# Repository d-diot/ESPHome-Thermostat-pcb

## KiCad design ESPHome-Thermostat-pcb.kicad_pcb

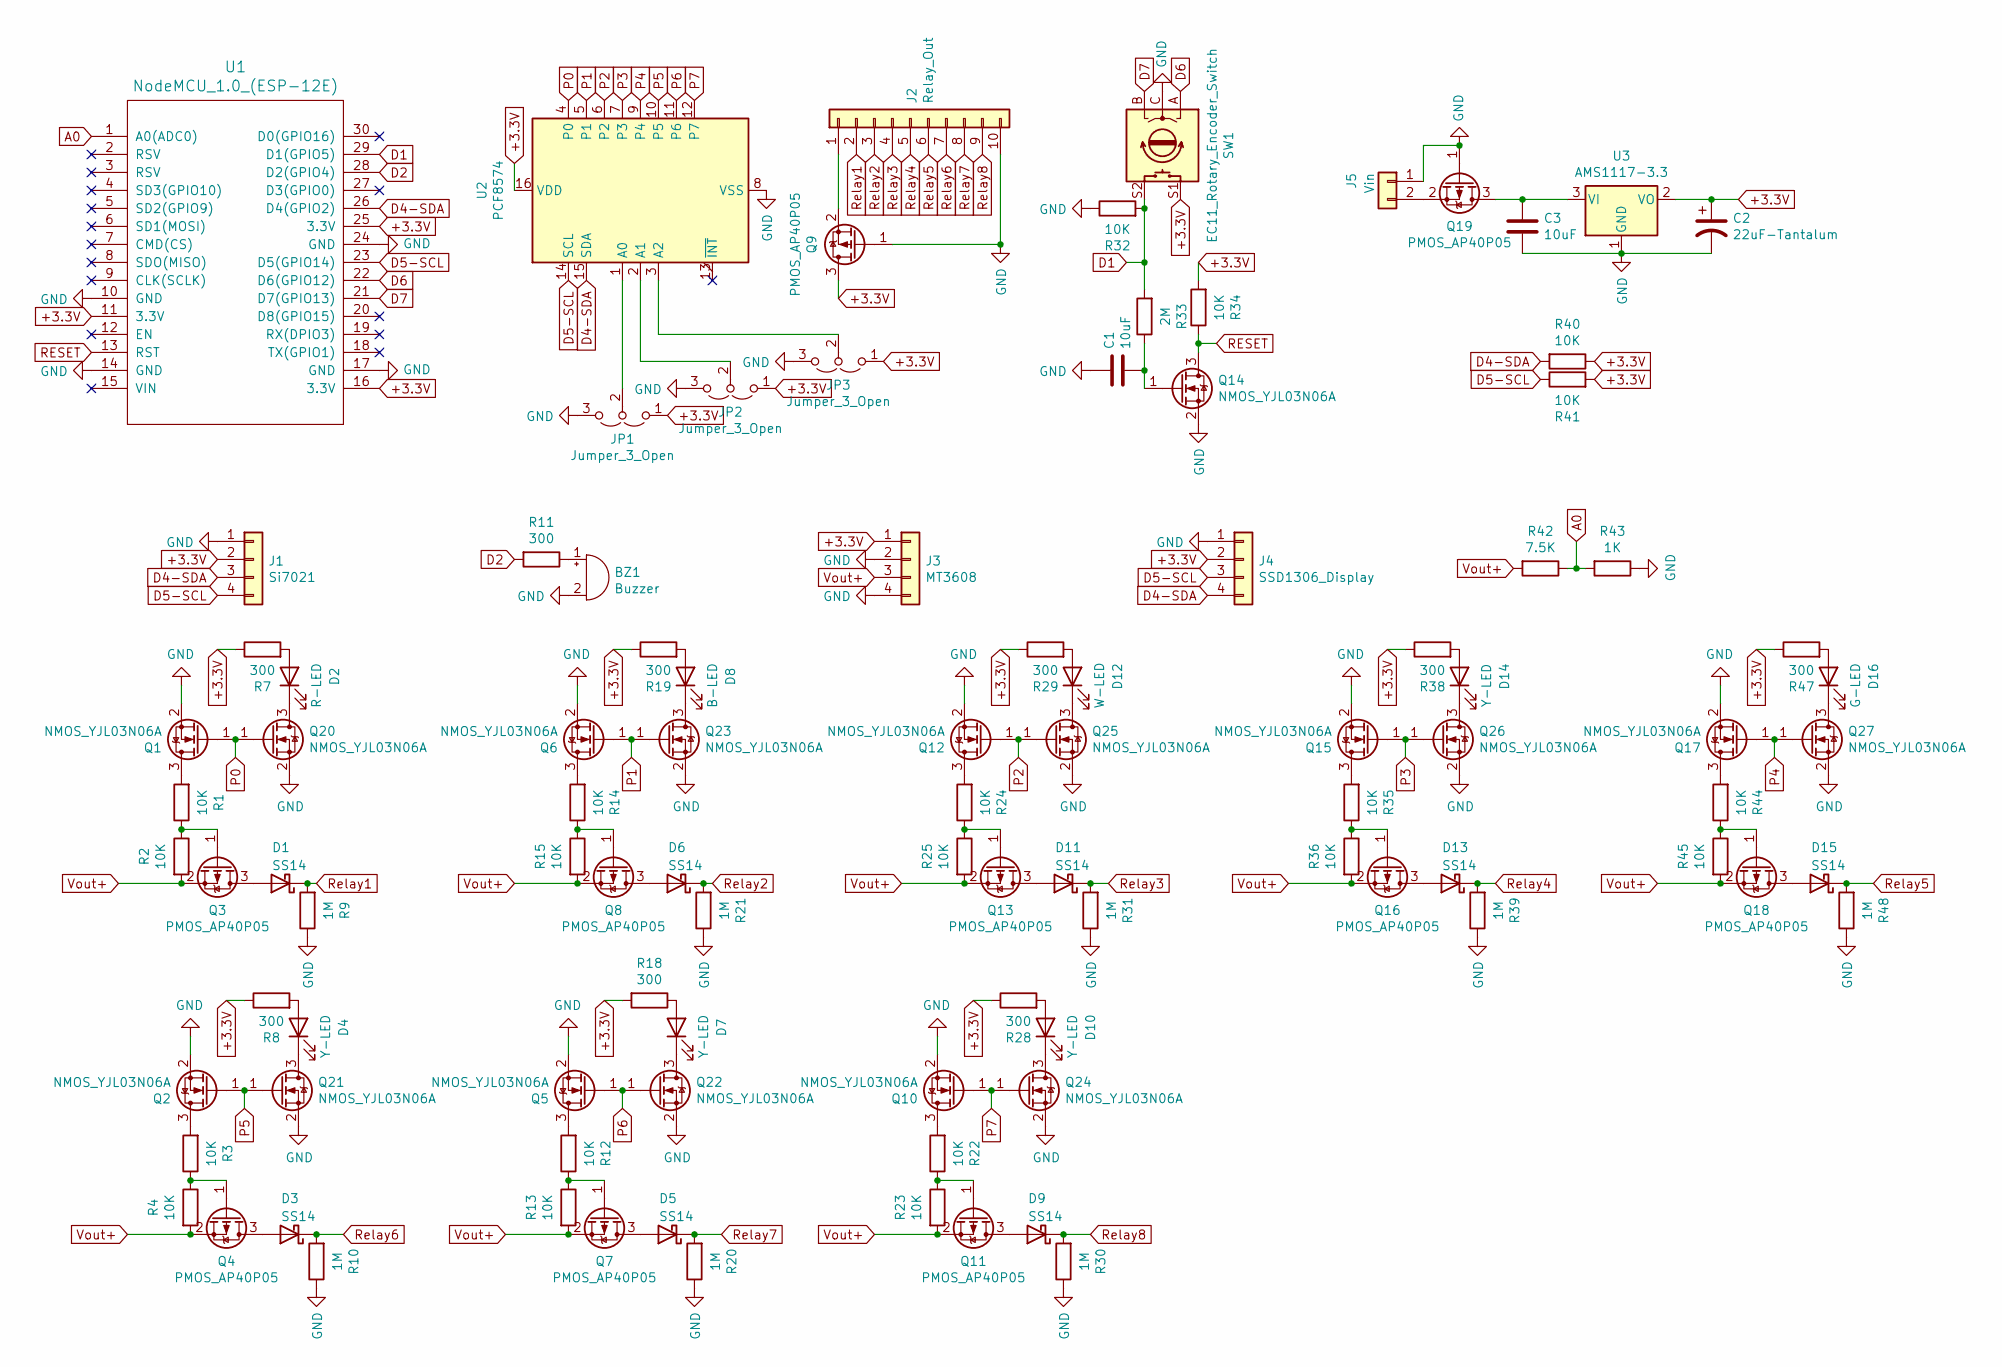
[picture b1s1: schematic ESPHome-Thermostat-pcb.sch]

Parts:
BZ1: Buzzer; Buzzer_12x9.5RM7.6; MPN NA
C1, C3: 10uF; C_0805_2012Metric; MPN CL21A106KAYNNNE
C2: 22uF-Tantalum; CAPPC3528X210N; MPN TAJB226M016RNJ
D1, D3, D5, D6, D9, D11, D13, D15: SS14; D_SMA; MPN SS14
D2: R-LED; LED_0805_2012Metric; MPN BL-HUE35A-AV-TRE
D4, D7, D10, D14: Y-LED; LED_0805_2012Metric; MPN NCD0805Y1
D8: B-LED; LED_0805_2012Metric; MPN NCD0805B2
D12: W-LED; LED_0805_2012Metric; MPN SZYY0805W
D16: G-LED; LED_0805_2012Metric; MPN NCD0805G1
J1: Si7021; PinSocket_1x04_P2.54mm_Vertical; MPN NA
J2: Relay_Out; TerminalBlock_4Ucon_1x10_P3.50mm_Vertical; MPN NA
J3: MT3608; MPN NA
J4: SSD1306_Display; Display_128x64_096_I2C; MPN NA
J5: Vin; TerminalBlock_4Ucon_1x02_P3.50mm_Vertical; MPN NA
JP1, JP2, JP3: Jumper_3_Open; SolderJumper-3_P2.0mm_Open_TrianglePad1.0x1.5mm_NumberLabels; MPN NA
Q1, Q2, Q5, Q6, Q10, Q12, Q14, Q15, Q17, Q20, Q21, Q22, Q23, Q24, Q25, Q26, Q27: NMOS_YJL03N06A; SOT-23; MPN YJL03N06A
Q3, Q4, Q7, Q8, Q9, Q11, Q13, Q16, Q18, Q19: PMOS_AP40P05; SOT-23; MPN AP40P05
R1, R2, R3, R4, R12, R13, R14, R15, R22, R23, R24, R25, R32, R34, R35, R36, R40, R41, R44, R45: 10K; R_0805_2012Metric; MPN TC0550F1002T5E
R7, R8, R11, R18, R19, R28, R29, R38, R47: 300; R_0805_2012Metric; MPN TC0525F3000T5E
R9, R10, R20, R21, R30, R31, R39, R48: 1M; R_0805_2012Metric; MPN TC0525F1004T5E
R33: 2M; R_0805_2012Metric; MPN FRC0805J205 TS
R42: 7.5K; R_0805_2012Metric; MPN 0805W8D7501T5E
R43: 1K; R_0805_2012Metric; MPN 0805W8D1001T5E
SW1: EC11_Rotary_Encoder_Switch; RotaryEncoder_Alps_EC11E-Switch_Vertical_H20mm; MPN EC11
U1: NodeMCU_1.0_(ESP-12E); NodeMCU-LoLinV3; MPN NA
U2: PCF8574; SOIC-16W_7.5x10.3mm_P1.27mm; MPN PCF8574T/3,518
U3: AMS1117-3.3; SOT-223-3_TabPin2; MPN AMS1117-3.3

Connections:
+3.3V: C2.1, J1.2, J3.1, J4.2, JP1.1 (A), JP2.1 (A), JP3.1 (A), Q9.3 (D), R7.1, R8.1, R18.2, R19.1, R28.1, R29.1, R34.2, R38.1, R40.1, R41.2, R47.1, SW1.S1, U1.11 (3.3V), U1.16 (3.3V), U1.25 (3.3V), U2.16 (VDD), U3.2 (VO)
A0: R42.1, R43.2, U1.1 (A0(ADC0))
D1: R32.2, R33.2, SW1.S2, U1.29 (D1(GPIO5))
D2: R11.2, U1.28 (D2(GPIO4))
D4-SDA: J1.3, J4.4, R40.2, U1.26 (D4(GPIO2)), U2.15 (SDA)
D5-SCL: J1.4, J4.3, R41.1, U1.23 (D5(GPIO14)), U2.14 (SCL)
D6: SW1.A, U1.22 (D6(GPIO12))
D7: SW1.B, U1.21 (D7(GPIO13))
GND: BZ1.2 (+), C1.1, C2.2, C3.2, J1.1, J2.10, J3.2, J3.4, J4.1, J5.1, JP1.3 (B), JP2.3 (B), JP3.3 (B), Q1.2 (S), Q2.2 (S), Q5.2 (S), Q6.2 (S), Q9.1 (G), Q10.2 (S), Q12.2 (S), Q14.2 (S), Q15.2 (S), Q17.2 (S), Q19.1 (G), Q20.2 (S), Q21.2 (S), Q22.2 (S), Q23.2 (S), Q24.2 (S), Q25.2 (S), Q26.2 (S), Q27.2 (S), R9.1, R10.1, R20.1, R21.1, R30.1, R31.1, R32.1, R39.1, R43.1, R48.1, SW1.C, U1.10 (GND), U1.14 (GND), U1.17 (GND), U1.24 (GND), U2.8 (VSS), U3.1 (GND)
unnamed: BZ1.1 (-), R11.1
unnamed: C1.2, Q14.1 (G), R33.1
unnamed: C3.1, Q19.3 (D), U3.3 (VI)
unnamed: D1.2 (A), Q3.3 (D)
unnamed: D2.1 (K), Q20.3 (D)
unnamed: D2.2 (A), R7.2
unnamed: D3.2 (A), Q4.3 (D)
unnamed: D4.1 (K), Q21.3 (D)
unnamed: D4.2 (A), R8.2
unnamed: D5.2 (A), Q7.3 (D)
unnamed: D6.2 (A), Q8.3 (D)
unnamed: D7.1 (K), Q22.3 (D)
unnamed: D7.2 (A), R18.1
unnamed: D8.1 (K), Q23.3 (D)
unnamed: D8.2 (A), R19.2
unnamed: D9.2 (A), Q11.3 (D)
unnamed: D10.1 (K), Q24.3 (D)
unnamed: D10.2 (A), R28.2
unnamed: D11.2 (A), Q13.3 (D)
unnamed: D12.1 (K), Q25.3 (D)
unnamed: D12.2 (A), R29.2
unnamed: D13.2 (A), Q16.3 (D)
unnamed: D14.1 (K), Q26.3 (D)
unnamed: D14.2 (A), R38.2
unnamed: D15.2 (A), Q18.3 (D)
unnamed: D16.1 (K), Q27.3 (D)
unnamed: D16.2 (A), R47.2
unnamed: J2.1, Q9.2 (S)
unnamed: J5.2, Q19.2 (S)
unnamed: JP1.2 (C), U2.1 (A0)
unnamed: JP2.2 (C), U2.2 (A1)
unnamed: JP3.2 (C), U2.3 (A2)
unnamed: Q1.3 (D), R1.2
unnamed: Q2.3 (D), R3.2
unnamed: Q3.1 (G), R1.1, R2.1
unnamed: Q4.1 (G), R3.1, R4.1
unnamed: Q5.3 (D), R12.2
unnamed: Q6.3 (D), R14.2
unnamed: Q7.1 (G), R12.1, R13.1
unnamed: Q8.1 (G), R14.1, R15.1
unnamed: Q10.3 (D), R22.2
unnamed: Q11.1 (G), R22.1, R23.1
unnamed: Q12.3 (D), R24.2
unnamed: Q13.1 (G), R24.1, R25.1
unnamed: Q15.3 (D), R35.2
unnamed: Q16.1 (G), R35.1, R36.1
unnamed: Q17.3 (D), R44.2
unnamed: Q18.1 (G), R44.1, R45.1
P0: Q1.1 (G), Q20.1 (G), U2.4 (P0)
P1: Q6.1 (G), Q23.1 (G), U2.5 (P1)
P2: Q12.1 (G), Q25.1 (G), U2.6 (P2)
P3: Q15.1 (G), Q26.1 (G), U2.7 (P3)
P4: Q17.1 (G), Q27.1 (G), U2.9 (P4)
P5: Q2.1 (G), Q21.1 (G), U2.10 (P5)
P6: Q5.1 (G), Q22.1 (G), U2.11 (P6)
P7: Q10.1 (G), Q24.1 (G), U2.12 (P7)
RESET: Q14.3 (D), R34.1, U1.13 (RST)
Relay1: D1.1 (K), J2.2, R9.2
Relay2: D6.1 (K), J2.3, R21.2
Relay3: D11.1 (K), J2.4, R31.2
Relay4: D13.1 (K), J2.5, R39.2
Relay5: D15.1 (K), J2.6, R48.2
Relay6: D3.1 (K), J2.7, R10.2
Relay7: D5.1 (K), J2.8, R20.2
Relay8: D9.1 (K), J2.9, R30.2
Vout+: J3.3, Q3.2 (S), Q4.2 (S), Q7.2 (S), Q8.2 (S), Q11.2 (S), Q13.2 (S), Q16.2 (S), Q18.2 (S), R2.2, R4.2, R13.2, R15.2, R23.2, R25.2, R36.2, R42.2, R45.2

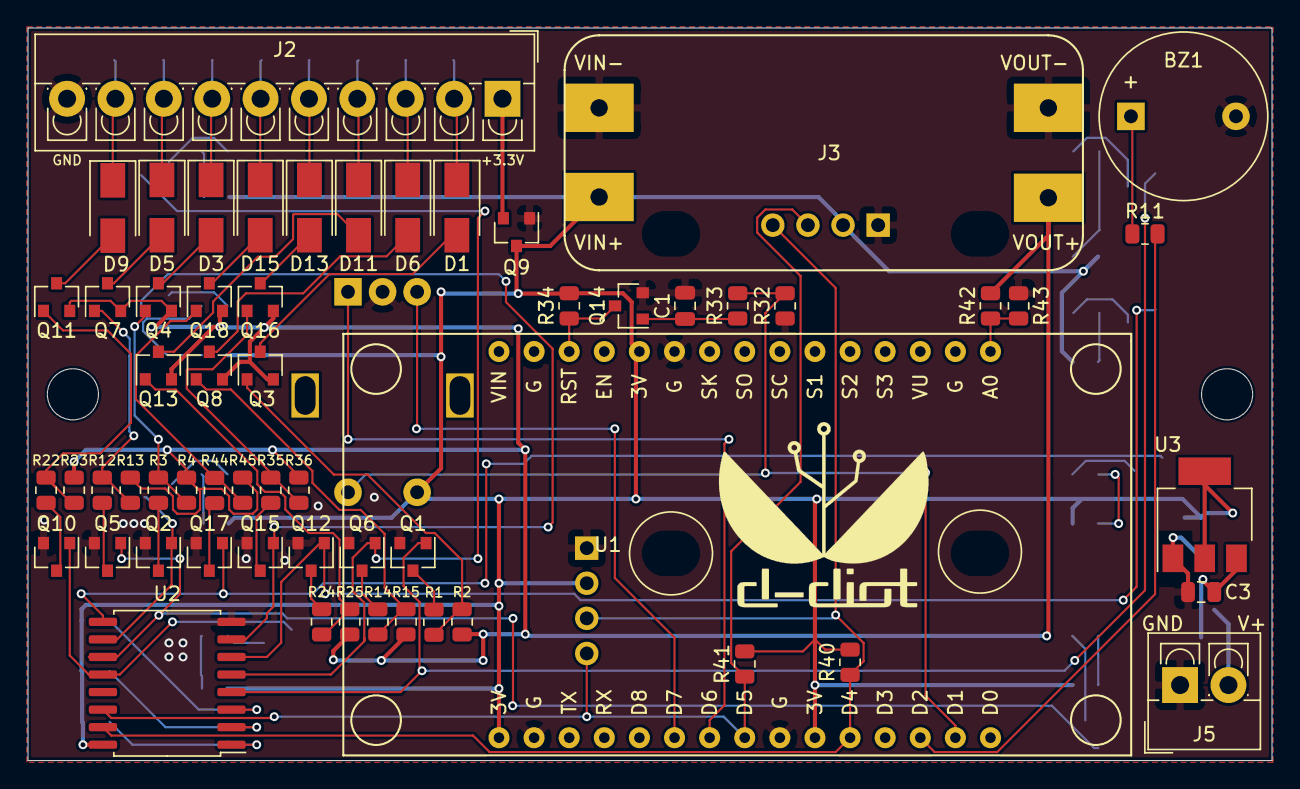
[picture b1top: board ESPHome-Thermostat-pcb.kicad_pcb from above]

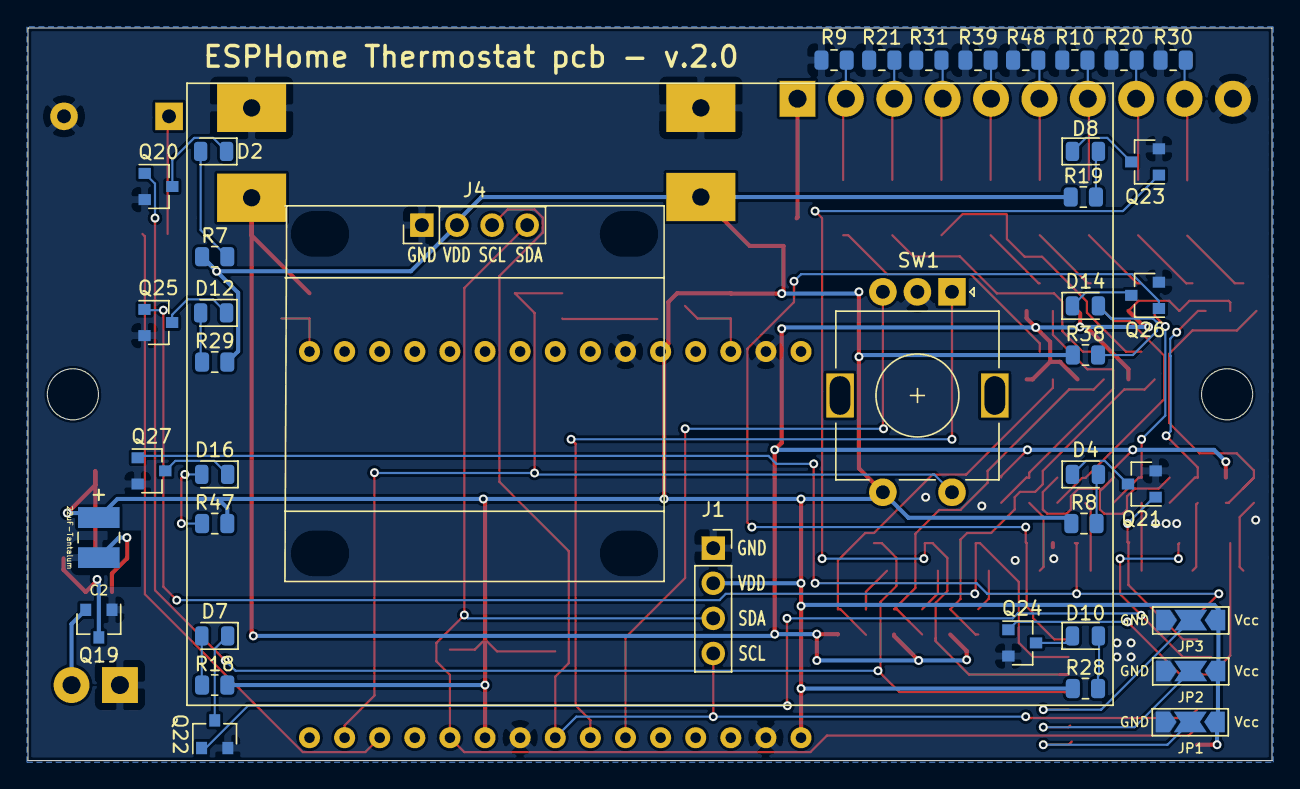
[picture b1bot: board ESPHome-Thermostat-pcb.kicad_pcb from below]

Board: 2 copper layers, 90.0 x 53.0 mm, 99 parts (40 on the bottom side), 75 nets.

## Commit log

2021-12-27 development
2022-01-09 Release board v.1.0
2022-02-08 Development v.2.0
2022-02-11 Release board v.2.0
